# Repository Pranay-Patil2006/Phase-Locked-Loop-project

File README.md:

# Phase-Locked-Loop Project

**This Project was part of EE322: Analog and Mixed Signal Circuits Course**
**Design and implementation on PCB of a phase-locked loop**

---

## Summary
Designed, simulated, and validated a discrete analog Phase-Locked Loop (PLL) implemented on PCB using a CD4046 phase detector, discrete op-amps, and passive/active loop-filter components. The design was optimized to minimize phase jitter and maximize capture and lock range, with close agreement between simulation and hardware measurements.

---

## Key Contributions
- **Loop design & analysis:** Derived loop-filter values from the closed-loop transfer function; verified lock time and stability margins using time-domain analysis.
- **Simulation strategy:** Performed LTSpice transient simulations and parameter sweeps to evaluate capture range, locking behavior, and sensitivity to component variations.
- **Jitter reduction tactics:** Reduced jitter through optimized loop bandwidth selection, low-noise op-amp choice, VCO linearization, proper supply decoupling, and careful PCB routing of phase detector and VCO control nodes.
- **Validation:** Conducted testbench measurements of lock acquisition and short-term phase stability to confirm simulation trends and guide final component tuning.

---

## Block Diagram

*Credits: https://electronicscoach.com/phase-locked-loops.html*

---

## Results
- **Measured capture/lock range:** 150Hz - 1300Hz

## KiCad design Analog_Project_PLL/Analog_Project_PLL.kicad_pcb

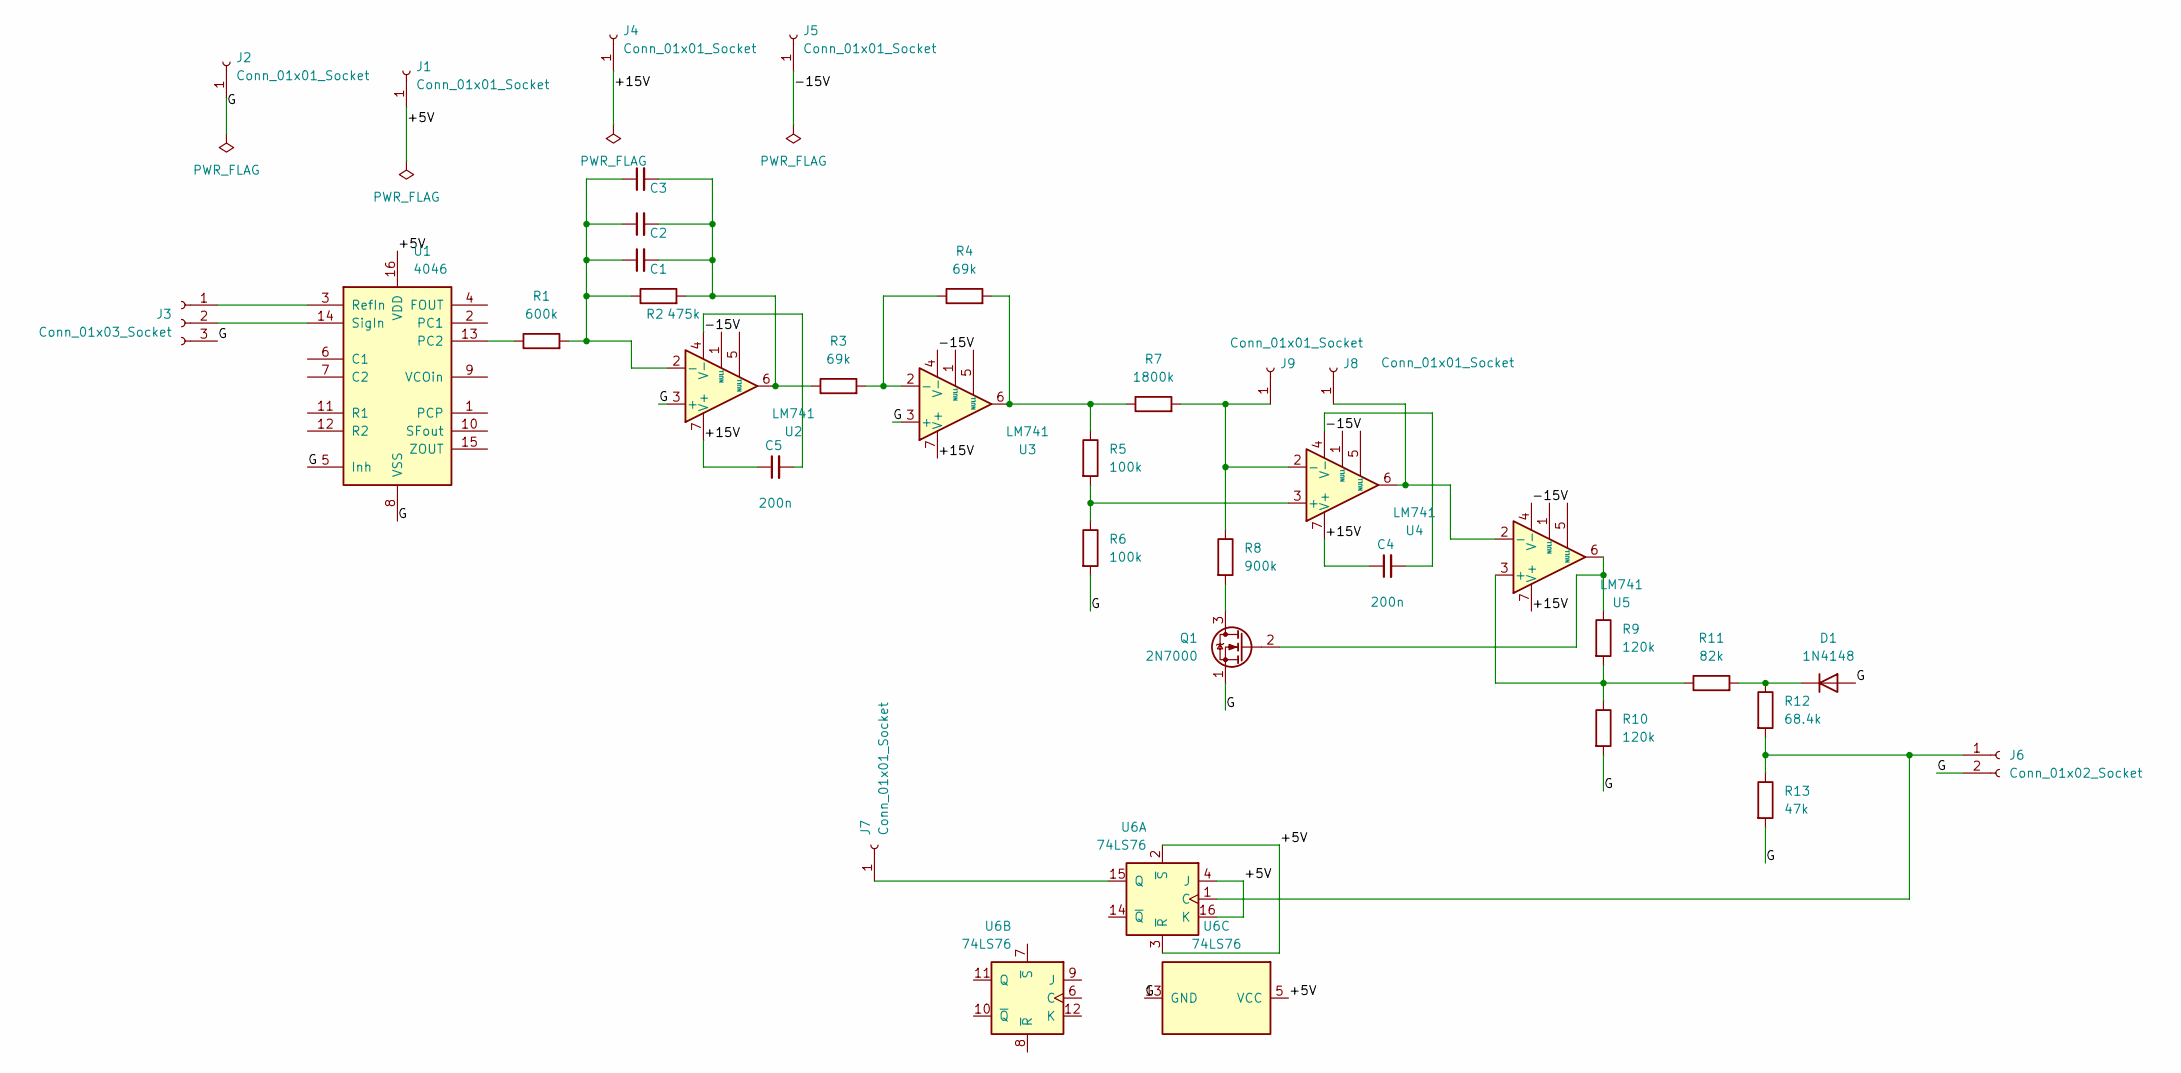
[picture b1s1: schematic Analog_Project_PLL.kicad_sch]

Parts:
C1, C2, C3: 33n; CP_Radial_D12.5mm_P7.50mm
C4, C5: 200n; CP_Radial_D12.5mm_P7.50mm
D1: 1N4148; D_DO-35_SOD27_P7.62mm_Horizontal
J1, J2, J4, J5, J7, J8, J9: Conn_01x01_Socket; PinSocket_1x01_P2.54mm_Vertical
J3: Conn_01x03_Socket; PinSocket_1x03_P2.54mm_Vertical
J6: Conn_01x02_Socket; PinSocket_1x02_P2.54mm_Vertical
Q1: 2N7000; TO-92_Inline
R1: 600k; R_Axial_DIN0309_L9.0mm_D3.2mm_P12.70mm_Horizontal
R2: 475k; R_Axial_DIN0309_L9.0mm_D3.2mm_P12.70mm_Horizontal
R3, R4: 69k; R_Axial_DIN0309_L9.0mm_D3.2mm_P12.70mm_Horizontal
R5, R6: 100k; R_Axial_DIN0309_L9.0mm_D3.2mm_P12.70mm_Horizontal
R7: 1800k; R_Axial_DIN0309_L9.0mm_D3.2mm_P12.70mm_Horizontal
R8: 900k; R_Axial_DIN0309_L9.0mm_D3.2mm_P12.70mm_Horizontal
R9, R10: 120k; R_Axial_DIN0309_L9.0mm_D3.2mm_P12.70mm_Horizontal
R11: 82k; R_Axial_DIN0309_L9.0mm_D3.2mm_P12.70mm_Horizontal
R12: 68.4k; R_Axial_DIN0309_L9.0mm_D3.2mm_P12.70mm_Horizontal
R13: 47k; R_Axial_DIN0309_L9.0mm_D3.2mm_P12.70mm_Horizontal
U1: 4046; DIP-16_W7.62mm
U2, U3, U4, U5: LM741; DIP-8_W7.62mm
U6: 74LS76; DIP-16_W7.62mm

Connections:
/+5V: J1.1, U1.16 (VDD), U6.2 (~S), U6.3 (~R), U6.4 (J), U6.5 (VCC), U6.16 (K)
/+15V: C4.1, C5.1, J4.1, U2.7 (V+), U3.7 (V+), U4.7 (V+), U5.7 (V+)
/-15V: C4.2, C5.2, J5.1, U2.4 (V-), U3.4 (V-), U4.4 (V-), U5.4 (V-)
/G: D1.2 (A), J2.1, J3.3, J6.2, Q1.1 (S), R6.2, R10.2, R13.2, U1.5 (Inh), U1.8 (VSS), U2.3 (+), U3.3 (+), U6.13 (GND)
unnamed: C1.2, C2.2, C3.2, R2.2, R3.1, U2.6
unnamed: D1.1 (K), R11.2, R12.1
unnamed: J3.1, U1.3 (RefIn)
unnamed: J3.2, U1.14 (SigIn)
unnamed: J6.1, R12.2, R13.1, U6.1 (C)
unnamed: J7.1, U6.15 (Q)
unnamed: J8.1, U4.6, U5.2 (-)
unnamed: J9.1, R7.2, R8.1, U4.2 (-)
unnamed: Q1.3 (D), R8.2
unnamed: Q1.2 (G), R9.1, U5.6
unnamed: R4.2, R5.1, R7.1, U3.6
unnamed: R1.1, U1.13 (PC2)
unnamed: C1.1, C2.1, C3.1, R1.2, R2.1, U2.2 (-)
unnamed: R3.2, R4.1, U3.2 (-)
unnamed: R5.2, R6.1, U4.3 (+)
unnamed: R9.2, R10.1, R11.1, U5.3 (+)

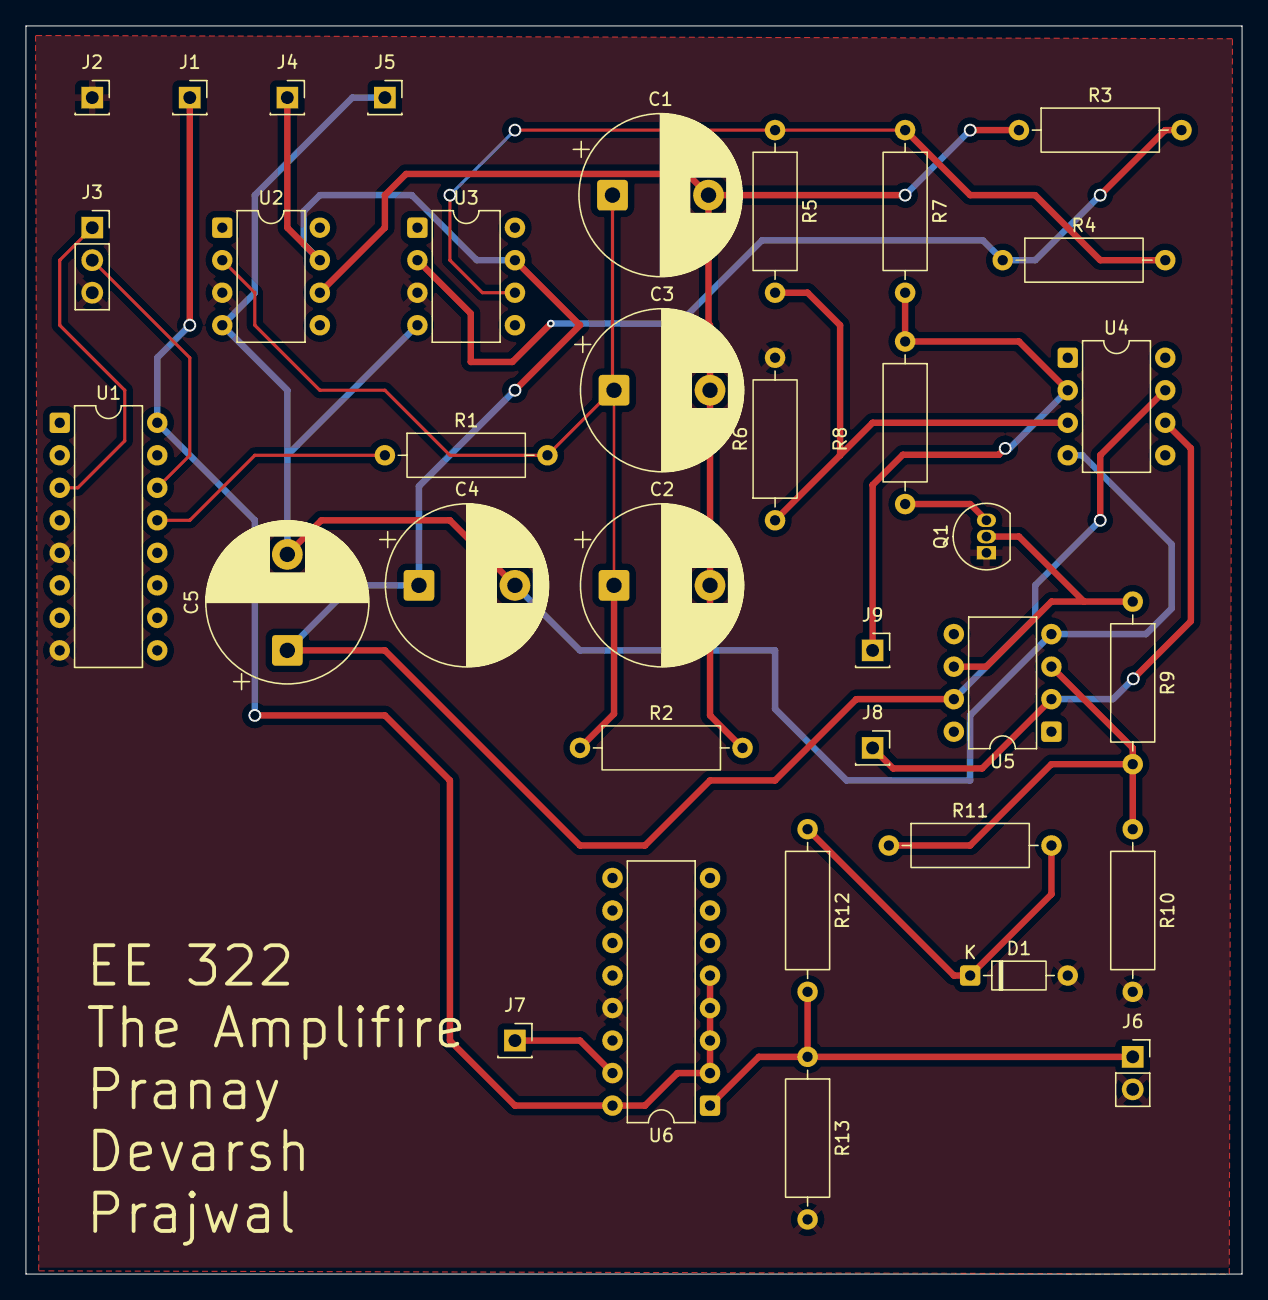
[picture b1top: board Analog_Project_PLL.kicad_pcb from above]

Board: 2 copper layers, 95.0 x 97.5 mm, 35 parts (0 on the bottom side), 20 nets.
